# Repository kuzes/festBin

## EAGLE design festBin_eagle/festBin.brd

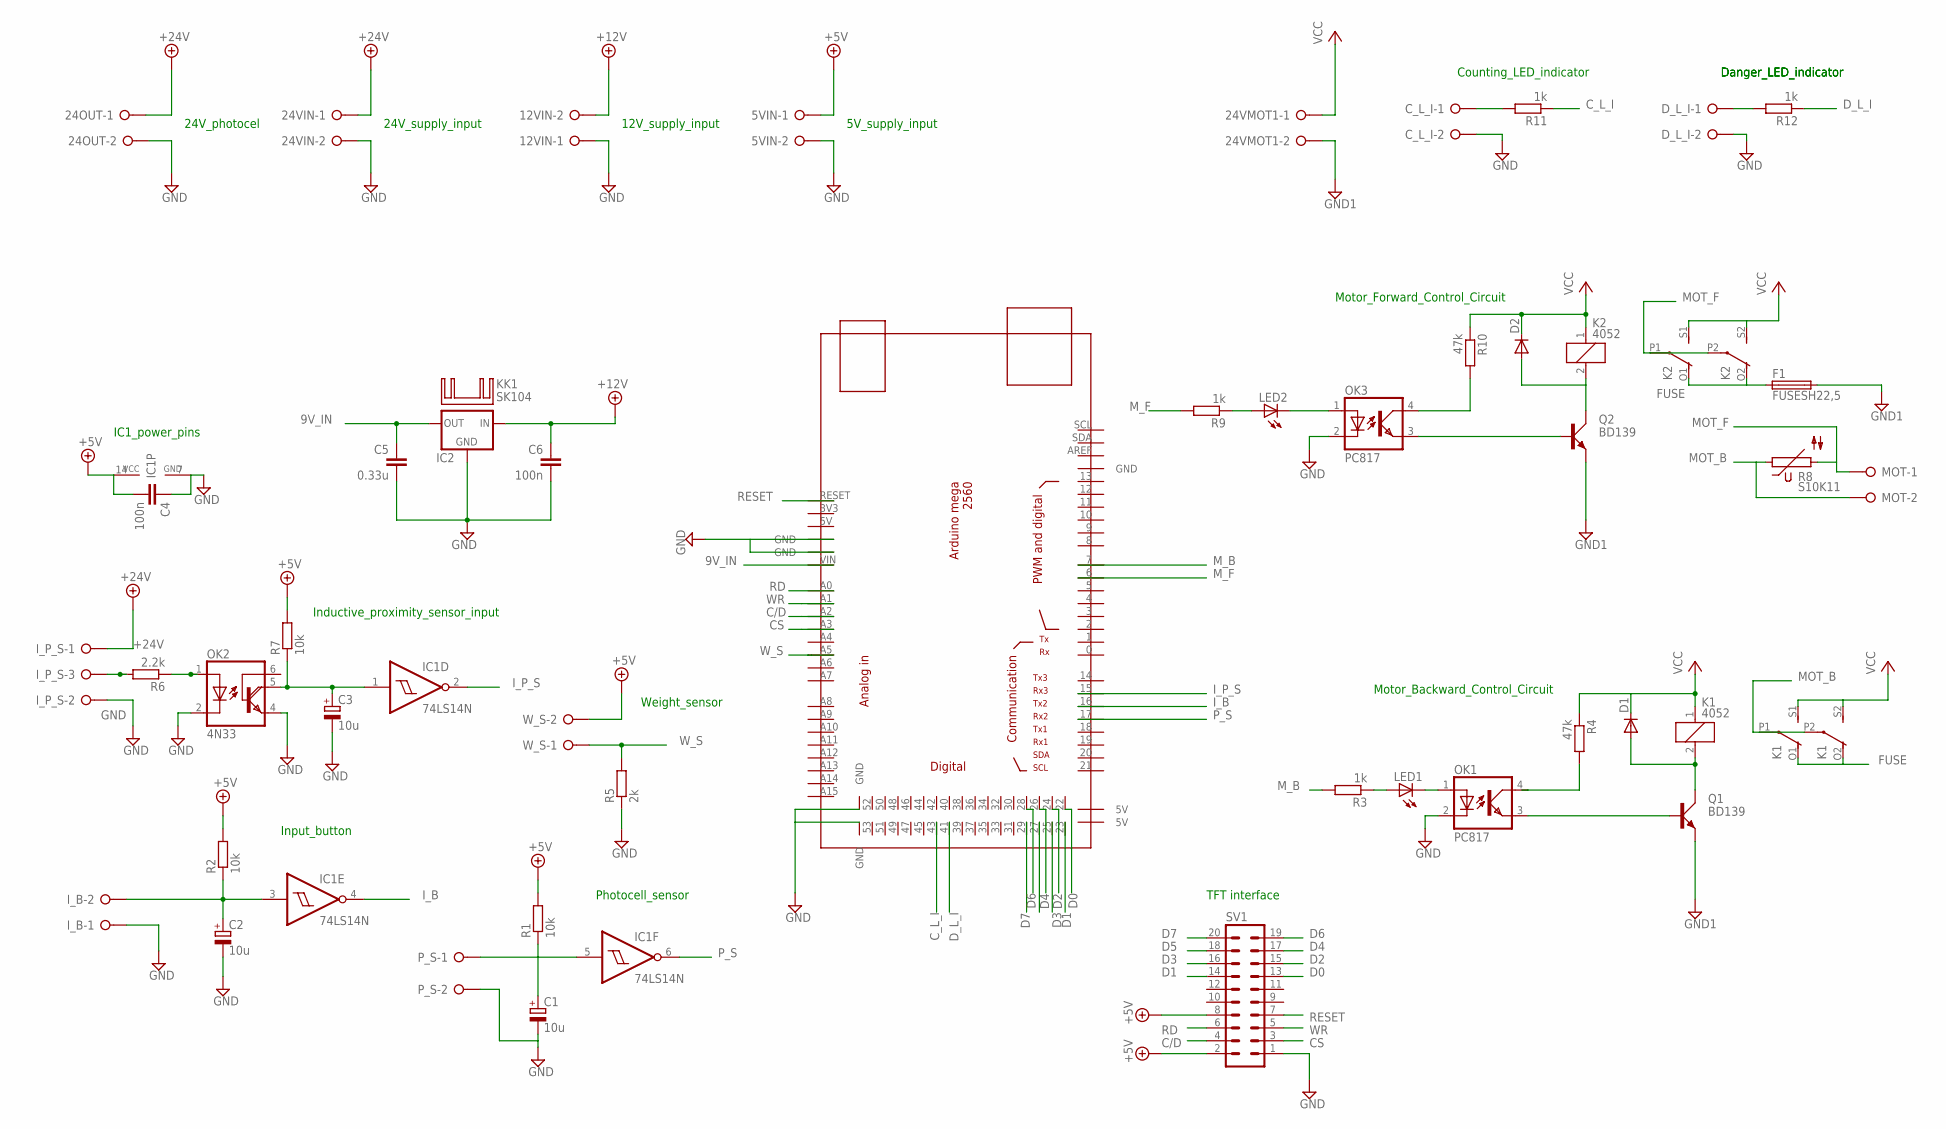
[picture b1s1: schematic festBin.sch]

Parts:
5VIN, 12VIN, 24OUT, 24VIN, 24VMOT1: W237-02P; W237-132
C1, C2, C3: 10u; E2,5-6
C4, C6: 100n; C050-024X044
C5: 0.33u; C050-024X044
C_L_I: W237-02P; W237-132
D1, D2: DIODE-DO41-10; DO41-10
D_L_I: W237-02P; W237-132
F1: FUSESH22,5; SH22,5
IC1: 74LS14N; DIL14
IC2: 78XXS
I_B: W237-02P; W237-132
I_P_S: W237-3E
K1, K2: 4052; F4052
KK1: SK104
LED1, LED2: LED3MM
MOT: W237-02P; W237-132
OK1, OK3: PC817; DIL04
OK2: 4N33; DIL06
P_S: W237-02P; W237-132
Q1, Q2: BD139; TO126AV
R1, R2, R7: 10k; 0207/10
R3, R9, R11, R12: 1k; 0207/10
R4, R10: 47k; 0207/10
R5: 2k; 0207/10
R6: 2.2k; 0207/10
R8: S10K11
SV1: ML20
U$1: MEGA_DEVICE; MEGABOX
W_S: W237-02P; W237-132

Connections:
9V_IN: C5.1, IC2.OUT, U$1.VIN
+5V: 5VIN.1, C4.2, IC1.14 (VCC), R1.2, R2.2, R7.2, SV1.2, SV1.8, W_S.2
+12V: 12VIN.2, C6.1, IC2.IN
+24V: 24OUT.1, 24VIN.1, I_P_S.1
C/D: SV1.4, U$1.A2
CS: SV1.3, U$1.A3
C_L_I: R11.1, U$1.43
D0: SV1.13, U$1.22
D1: SV1.14, U$1.23
D2: SV1.15, U$1.24
D3: SV1.16, U$1.25
D4: SV1.17, U$1.26
D5: SV1.18, U$1.27
D6: SV1.19, U$1.28
D7: SV1.20, U$1.29
D_L_I: R12.1, U$1.41
FUSE: F1.1, K1.O1 (O), K1.O2 (O), K2.O1 (O), K2.O2 (O)
GND: 5VIN.2, 12VIN.1, 24OUT.2, 24VIN.2, C1.-, C2.-, C3.-, C4.1, C5.2, C6.2, C_L_I.2, D_L_I.2, IC1.7 (GND), IC2.GND, I_B.1, I_P_S.2, OK1.2 (C), OK2.2 (C), OK2.4 (E), OK3.2 (C), P_S.2, R5.1, SV1.1, U$1.GND@2 (GND), U$1.GND@3 (GND), U$1.GND@6 (GND), U$1.GND@7 (GND)
GND1: 24VMOT1.2, F1.2, Q1.E, Q2.E
I_B: IC1.4 (O), U$1.16
I_P_S: IC1.2 (O), U$1.15
MOT_B: K1.P1, K1.P2, MOT.2, R8.1
MOT_F: K2.P1, K2.P2, MOT.1, R8.2
M_B: R3.2, U$1.7
M_F: R9.2, U$1.6
unnamed: I_P_S.3, R6.2
unnamed: C1.+, IC1.5 (I), P_S.1, R1.1
unnamed: C_L_I.1, R11.2
unnamed: D_L_I.1, R12.2
unnamed: C2.+, IC1.3 (I), I_B.2, R2.1
unnamed: LED2.A, R9.1
unnamed: LED1.A, R3.1
unnamed: OK3.4 (COL), R10.2
unnamed: OK1.3 (EMIT), Q1.B
unnamed: D2.A, K2.2, Q2.C
unnamed: LED1.K (C), OK1.1 (A)
unnamed: LED2.K (C), OK3.1 (A)
unnamed: OK1.4 (COL), R4.2
unnamed: D1.A, K1.2, Q1.C
unnamed: OK3.3 (EMIT), Q2.B
unnamed: OK2.1 (A), R6.1
unnamed: C3.+, IC1.1 (I), OK2.5 (COL), R7.1
P_S: IC1.6 (O), U$1.17
RD: SV1.6, U$1.A0
RESET: SV1.7, U$1.RESET
VCC: 24VMOT1.1, D1.C, D2.C, K1.1, K1.S1 (S), K1.S2 (S), K2.1, K2.S1 (S), K2.S2 (S), R4.1, R10.1
WR: SV1.5, U$1.A1
W_S: R5.2, U$1.A5, W_S.1

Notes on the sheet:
Inductive_proximity_sensor_input
IC1_power_pins
Counting_LED_indicator
Danger_LED_indicator
Input_button
Weight_sensor
24V_supply_input
Motor_Forward_Control_Circuit
Motor_Backward_Control_Circuit
24V_photocel
Photocell_sensor
5V_supply_input
12V_supply_input
TFT interface

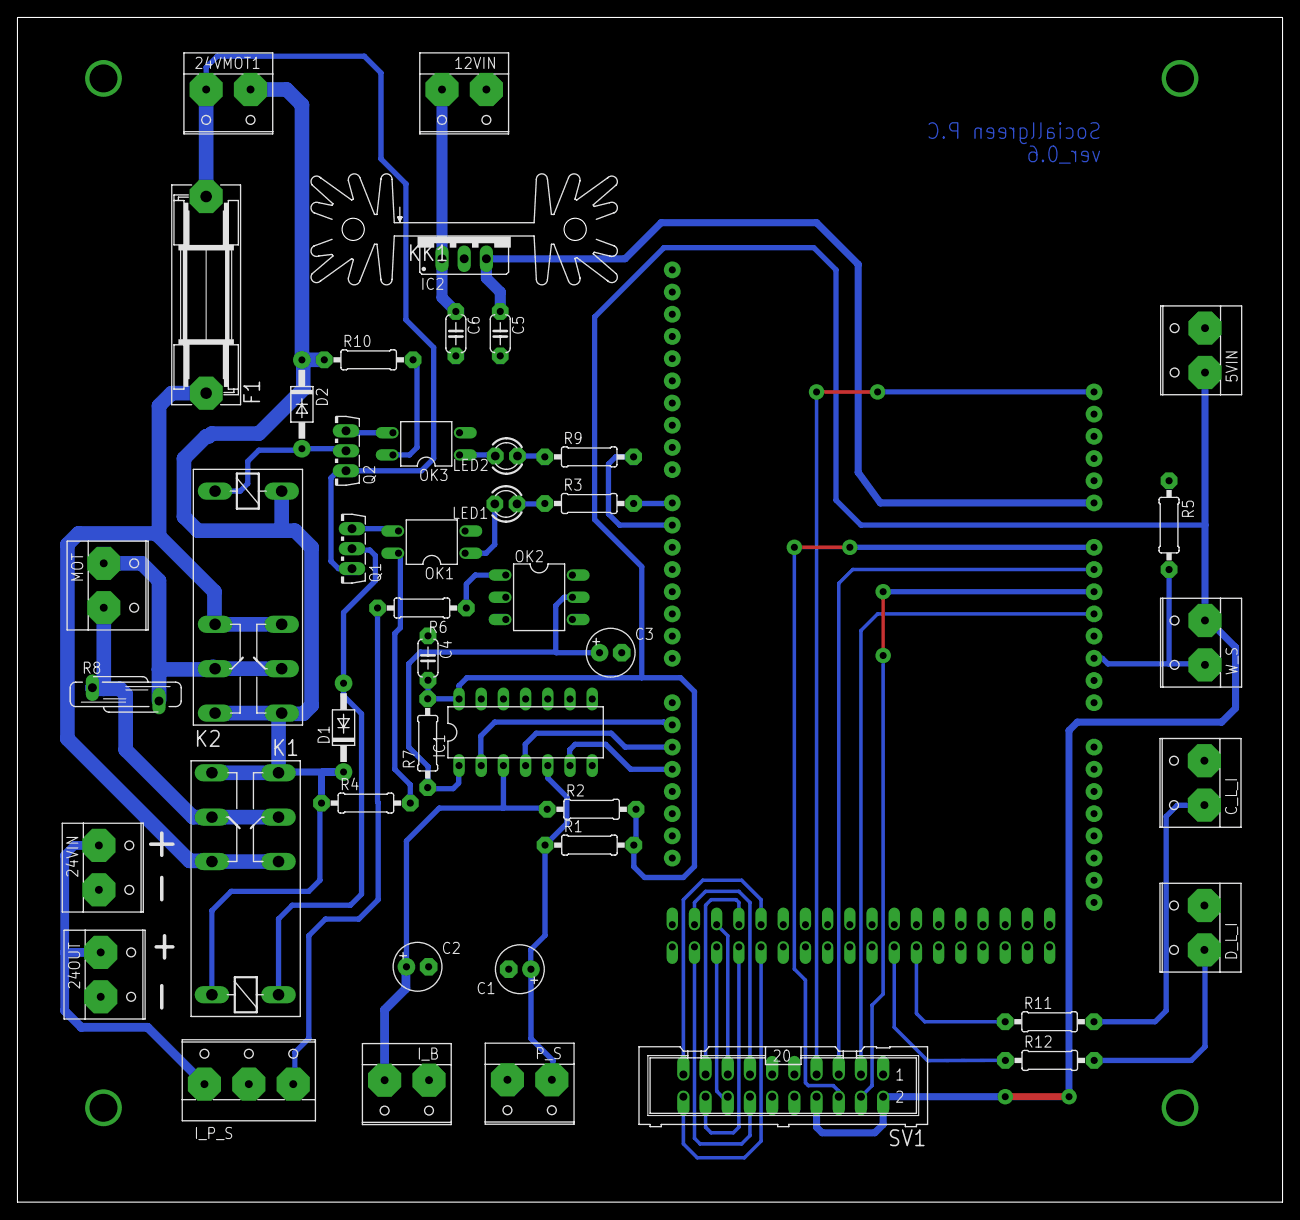
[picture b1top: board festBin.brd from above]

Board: 2 copper layers, 144.8 x 135.6 mm, 47 parts (1 on the bottom side), 48 nets.

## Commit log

2013-10-14 ver_0.6
2013-10-18 ver_0.6_clean
